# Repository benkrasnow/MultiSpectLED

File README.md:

# MultiSpectLED
Array of 15 1W LEDs spanning 280nm to 940nm

Notes:  The 280nm LED has a forward voltage drop of between 5V and 7.5V depending on the voltage bin.  This is higher that I expected when I designed the circuit, and it will not work if the power supply is really 5.0V.  It should have a boost converter instead of a buck converter.  However, I happened to receive an LED with a 5.1V drop, and my 5V wall adapter supplies 5.35V at 500mA, so the system works with the buck converter, just barely.  This part of the circuit should be redesigned if 280nm is needed.

UPDATE:  I added 0402 resistors near each buck controller.
The "enable" pin on the PAM2804 buck controller is very high-impedance, and will float around while the MCU is being programmed.  This causes bright flashes, and potentially can draw too much current from the supply, so pull-down resistors *MUST* be added between each PWM control line and ground.  I haven't updated the PCB yet, and fixed it in the prototype by adding resistors:

The heatsink has a 45mm wide rasied section, and the PCB is designed so that all exposed copper is ground within this 45mm strip. I used the PCB itself as a drill guide to drill 2.5mm holes, and then tapped them M3.  I used M3x4 screws to hold the PCB to the heatsink.

Originally, I planned to use Luxeon IR LEDs from Lumileds for the 850 and 940nm.  The thermal pad on these is tied to the anode, so it will not work with the current PCB design. I replaced them with alternate parts with very similar footprint, and have updated the BOM and layout.  

Heatsink and fan: https://www.amazon.com/dp/B00006B8EX
The fan runs nice and quiet on 5V, and provides more than enough airflow

USB-C 5V 4A power adapter:  Digikey 1597-106060004-ND  This should have enough current capacity to run up to 8 LEDs at full power.

Each LED channel is configured for 500mA , which is set by the 0.2 ohm resistor and internal 0.1V reference of the buck controller IC, PAM2804.
Dimming is achieved with PWM, and I used "software PWM" to get 15 separate channels from the Teensy-LC.  The SoftPWM library defaults to 60Hz update, which I noticed flickering, so I edited SoftPWM.cpp to use 120Hz instead.  MCUs with 15+ hardware PWM channels exist, but are more expensive, and not easy to find these days!

The Teensy-LC also provides easy programability for external triggering, remote control via USB serial, etc

The +5V power connection on the Teensy-LC between its USB micro plug and Vin pin should be cut.  There is a thin link between two exposed pads on the underside for this purpose.  This allows the Teensy to be powered only by the Vin pin, which is connected to the USB-C power rail in this design (it must be powered for programming).  If the link is not cut, and both USB connections are made with mismatched voltages (eg 4.9V vs 5.3V), bad currents may flow.

Total cost is about $180, and the 280nm LED alone is $24

.

Thermal performance looks very good.  At 16C ambient, the hottest part is the inductor at 23C.

Device was used to create Silver nanoprisms grown into structural colors by high power LEDs

A video can be found here - https://www.youtube.com/watch?v=v8pko9IlFW4

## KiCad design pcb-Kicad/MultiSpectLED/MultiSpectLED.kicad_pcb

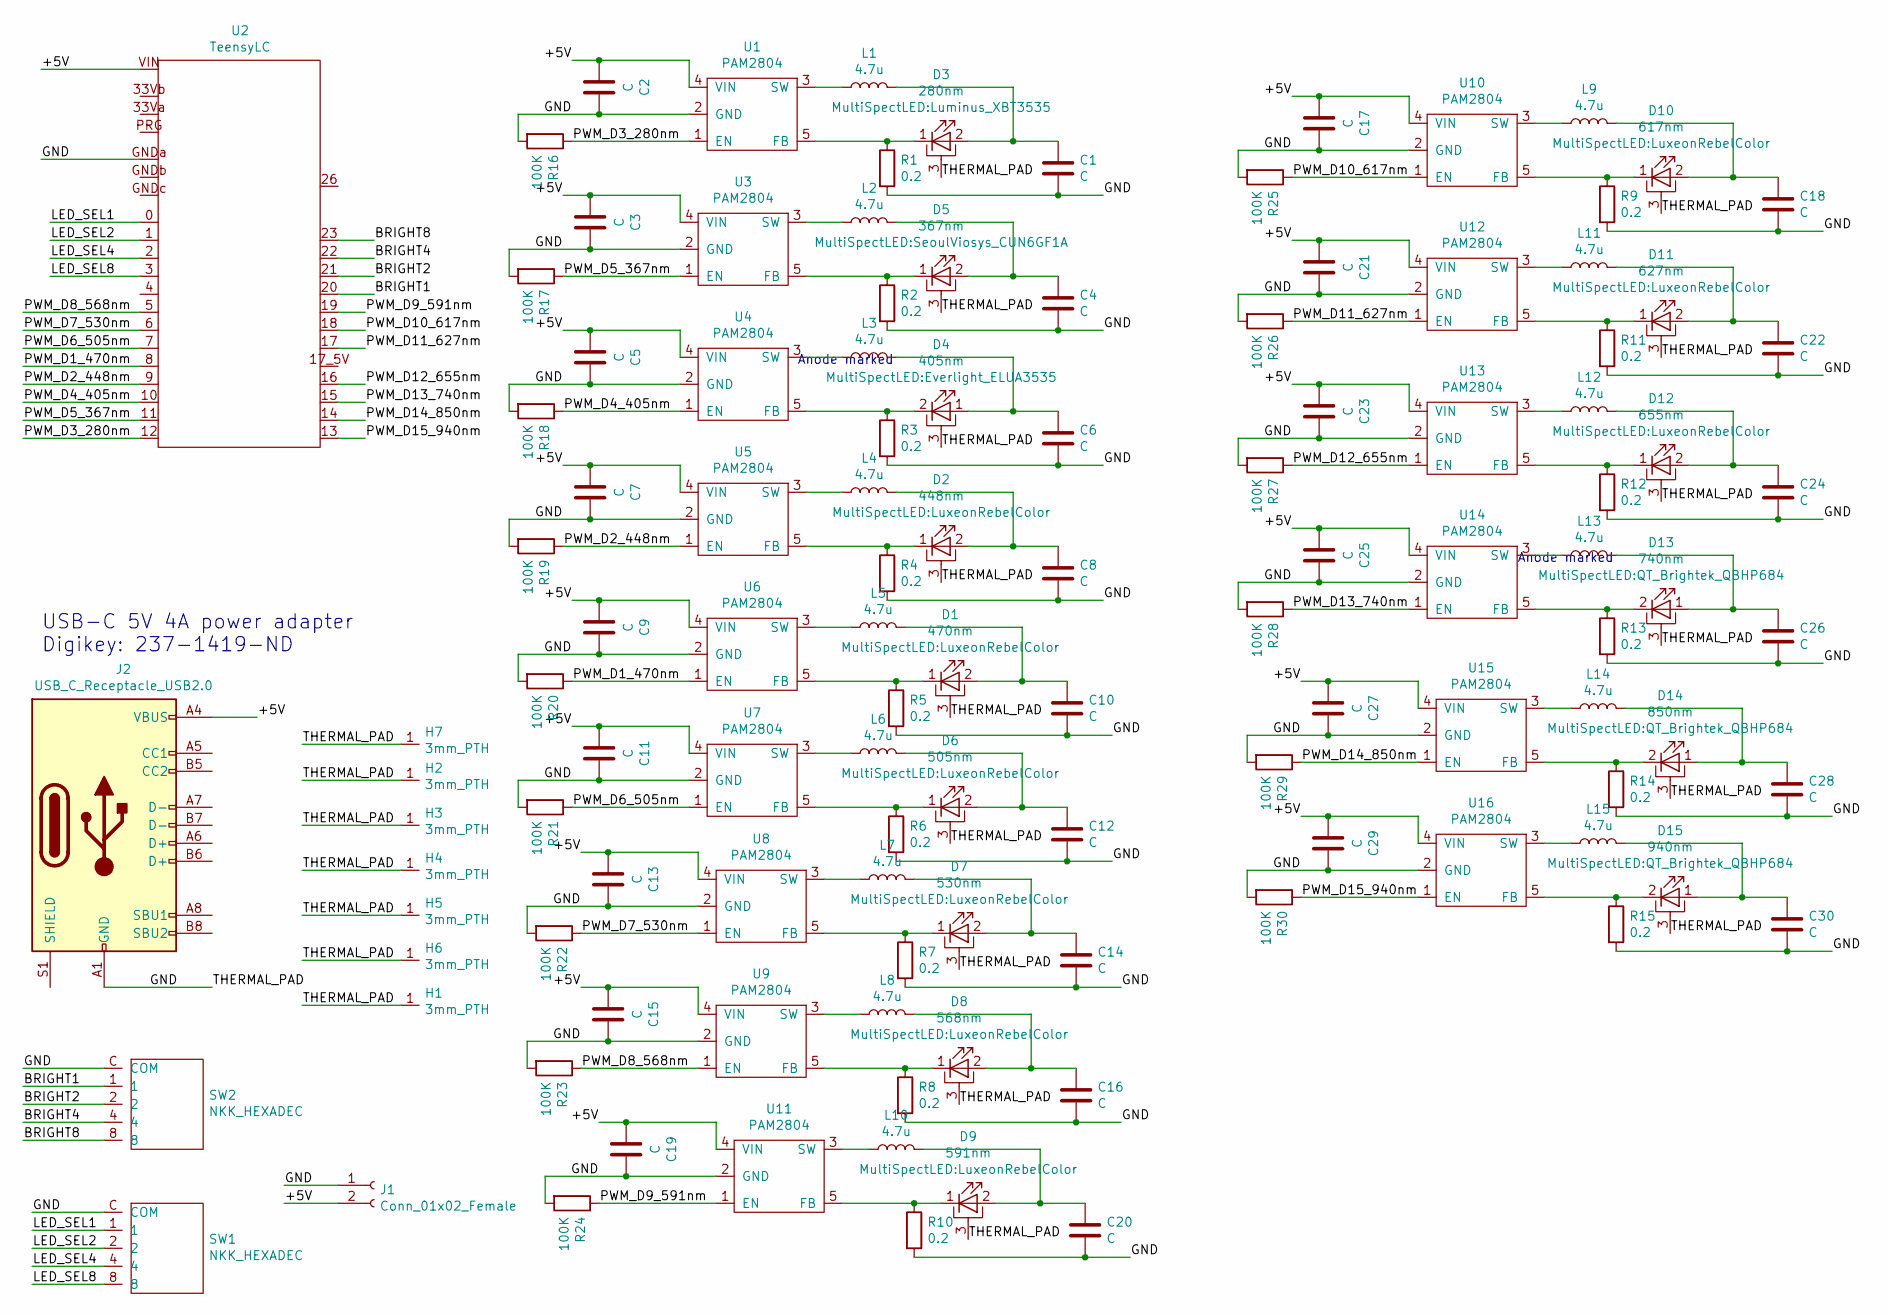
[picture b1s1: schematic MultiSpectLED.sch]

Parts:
C1, C2, C3, C4, C5, C6, C7, C8, C9, C10, C11, C12, C13, C14, C15, C16, C17, C18, C19, C20, C21, C22, C23, C24, C25, C26, C27, C28, C29, C30: C; C_0805_2012Metric; Digikey Part Number 490-3886-1-ND
D1: 470nm; LuxeonRebelColor; Digikey Part Number 1416-1029-1-ND
D2: 448nm; LuxeonRebelColor; Digikey Part Number 1416-1038-1-ND
D3: 280nm; Luminus_XBT3535; Digikey Part Number 1214-XBT-3535-UV-A130-CD270-00CT-ND
D4: 405nm; Everlight_ELUA3535; Digikey Part Number 1080-1620-1-ND
D5: 367nm; SeoulViosys_CUN6GF1A; Digikey Part Number 2112-CUN6GF1ACT-ND
D6: 505nm; LuxeonRebelColor; Digikey Part Number 1416-1031-1-ND
D7: 530nm; LuxeonRebelColor; Digikey Part Number 1416-1036-1-ND
D8: 568nm; LuxeonRebelColor; Digikey Part Number 1416-1185-1-ND
D9: 591nm; LuxeonRebelColor; Digikey Part Number 1416-1027-1-ND
D10: 617nm; LuxeonRebelColor; Digikey Part Number 1416-1026-1-ND
D11: 627nm; LuxeonRebelColor; Digikey Part Number 1416-1024-1-ND
D12: 655nm; LuxeonRebelColor; Digikey Part Number 1416-1701-1-ND
D13: 740nm; QT_Brightek_QBHP684; Digikey Part Number 1516-1213-1-ND
D14: 850nm; QT_Brightek_QBHP684
D15: 940nm; QT_Brightek_QBHP684
H1, H2, H3, H4, H5, H6, H7: 3mm_PTH
J1: Conn_01x02_Female; FAN_PADS
J2: USB_C_Receptacle_USB2.0; USB_C_Receptacle_Amphenol_12401610E4-2A; Digikey Part Number CP-036AHPJCT-ND
L1, L2, L3, L4, L5, L6, L7, L8, L9, L10, L11, L12, L13, L14, L15: 4.7u; L_1007_2518Metric; Digikey Part Number 587-1621-1-ND
R1, R2, R3, R4, R5, R6, R7, R8, R9, R10, R11, R12, R13, R14, R15: 0.2; R_0805_2012Metric; Digikey Part Number RL12S.20FCT-ND
R16, R17, R18, R19, R20, R21, R22, R23, R24, R25, R26, R27, R28, R29, R30: 100K; R_0402_1005Metric; Digikey Part Number RC1005F104CS
SW1, SW2: NKK_HEXADEC; NKK_FR02; Digikey Part Number 360-2543-1-ND
U1, U3, U4, U5, U6, U7, U8, U9, U10, U11, U12, U13, U14, U15, U16: PAM2804; SOT-23-5; Digikey Part Number PAM2804AAB010DICT-ND
U2: TeensyLC; Digikey Part Number 1568-1233-ND

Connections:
/+5V: C2.2, C3.2, C5.2, C7.2, C9.2, C11.2, C13.2, C15.2, C17.2, C19.2, C21.2, C23.2, C25.2, C27.2, C29.2, J1.2, J2.A4 (VBUS), J2.A9 (VBUS), J2.B4 (VBUS), J2.B9 (VBUS), U1.4 (VIN), U2.VIN, U3.4 (VIN), U4.4 (VIN), U5.4 (VIN), U6.4 (VIN), U7.4 (VIN), U8.4 (VIN), U9.4 (VIN), U10.4 (VIN), U11.4 (VIN), U12.4 (VIN), U13.4 (VIN), U14.4 (VIN), U15.4 (VIN), U16.4 (VIN)
/BRIGHT1: SW2.1, U2.20
/BRIGHT2: SW2.2, U2.21
/BRIGHT4: SW2.4, U2.22
/BRIGHT8: SW2.8, U2.23
/GND: C1.2, C2.1, C3.1, C4.2, C5.1, C6.2, C7.1, C8.2, C9.1, C10.2, C11.1, C12.2, C13.1, C14.2, C15.1, C16.2, C17.1, C18.2, C19.1, C20.2, C21.1, C22.2, C23.1, C24.2, C25.1, C26.2, C27.1, C28.2, C29.1, C30.2, D1.3 (PAD), D2.3 (PAD), D3.3 (PAD), D4.3 (PAD), D5.3 (PAD), D6.3 (PAD), D7.3 (PAD), D8.3 (PAD), D9.3 (PAD), D10.3 (PAD), D11.3 (PAD), D12.3 (PAD), D13.3 (PAD), D14.3 (PAD), D15.3 (PAD), H1.1, H2.1, H3.1, H4.1, H5.1, H6.1, H7.1, J1.1, J2.A1 (GND), J2.A12 (GND), J2.B1 (GND), J2.B12 (GND), R1.2, R2.2, R3.2, R4.2, R5.2, R6.2, R7.2, R8.2, R9.2, R10.2, R11.2, R12.2, R13.2, R14.2, R15.2, R16.2, R17.2, R18.2, R19.2, R20.2, R21.2, R22.2, R23.2, R24.2, R25.2, R26.2, R27.2, R28.2, R29.2, R30.2, SW1.C (COM), SW2.C (COM), U1.2 (GND), U2.GNDa, U3.2 (GND), U4.2 (GND), U5.2 (GND), U6.2 (GND), U7.2 (GND), U8.2 (GND), U9.2 (GND), U10.2 (GND), U11.2 (GND), U12.2 (GND), U13.2 (GND), U14.2 (GND), U15.2 (GND), U16.2 (GND)
/LED_SEL1: SW1.1, U2.0
/LED_SEL2: SW1.2, U2.1
/LED_SEL4: SW1.4, U2.2
/LED_SEL8: SW1.8, U2.3
/PWM_D1_470nm: R20.1, U2.8, U6.1 (EN)
/PWM_D2_448nm: R19.1, U2.9, U5.1 (EN)
/PWM_D3_280nm: R16.1, U1.1 (EN), U2.12
/PWM_D4_405nm: R18.1, U2.10, U4.1 (EN)
/PWM_D5_367nm: R17.1, U2.11, U3.1 (EN)
/PWM_D6_505nm: R21.1, U2.7, U7.1 (EN)
/PWM_D7_530nm: R22.1, U2.6, U8.1 (EN)
/PWM_D8_568nm: R23.1, U2.5, U9.1 (EN)
/PWM_D9_591nm: R24.1, U2.19, U11.1 (EN)
/PWM_D10_617nm: R25.1, U2.18, U10.1 (EN)
/PWM_D11_627nm: R26.1, U2.17, U12.1 (EN)
/PWM_D12_655nm: R27.1, U2.16, U13.1 (EN)
/PWM_D13_740nm: R28.1, U2.15, U14.1 (EN)
/PWM_D14_850nm: R29.1, U2.14, U15.1 (EN)
/PWM_D15_940nm: R30.1, U2.13, U16.1 (EN)
unnamed: C1.1, D3.2 (A), L1.2
unnamed: C4.1, D5.2 (A), L2.2
unnamed: C6.1, D4.1 (A), L3.2
unnamed: C8.1, D2.2 (A), L4.2
unnamed: C10.1, D1.2 (A), L5.2
unnamed: C12.1, D6.2 (A), L6.2
unnamed: C14.1, D7.2 (A), L7.2
unnamed: C16.1, D8.2 (A), L8.2
unnamed: C18.1, D10.2 (A), L9.2
unnamed: C20.1, D9.2 (A), L10.2
unnamed: C22.1, D11.2 (A), L11.2
unnamed: C24.1, D12.2 (A), L12.2
unnamed: C26.1, D13.1 (A), L13.2
unnamed: C28.1, D14.1 (A), L14.2
unnamed: C30.1, D15.1 (A), L15.2
unnamed: D1.1 (K), R5.1, U6.5 (FB)
unnamed: D2.1 (K), R4.1, U5.5 (FB)
unnamed: D3.1 (K), R1.1, U1.5 (FB)
unnamed: D4.2 (K), R3.1, U4.5 (FB)
unnamed: D5.1 (K), R2.1, U3.5 (FB)
unnamed: D6.1 (K), R6.1, U7.5 (FB)
unnamed: D7.1 (K), R7.1, U8.5 (FB)
unnamed: D8.1 (K), R8.1, U9.5 (FB)
unnamed: D9.1 (K), R10.1, U11.5 (FB)
unnamed: D10.1 (K), R9.1, U10.5 (FB)
unnamed: D11.1 (K), R11.1, U12.5 (FB)
unnamed: D12.1 (K), R12.1, U13.5 (FB)
unnamed: D13.2 (K), R13.1, U14.5 (FB)
unnamed: D14.2 (K), R14.1, U15.5 (FB)
unnamed: D15.2 (K), R15.1, U16.5 (FB)
unnamed: L1.1, U1.3 (SW)
unnamed: L2.1, U3.3 (SW)
unnamed: L3.1, U4.3 (SW)
unnamed: L4.1, U5.3 (SW)
unnamed: L5.1, U6.3 (SW)
unnamed: L6.1, U7.3 (SW)
unnamed: L7.1, U8.3 (SW)
unnamed: L8.1, U9.3 (SW)
unnamed: L9.1, U10.3 (SW)
unnamed: L10.1, U11.3 (SW)
unnamed: L11.1, U12.3 (SW)
unnamed: L12.1, U13.3 (SW)
unnamed: L13.1, U14.3 (SW)
unnamed: L14.1, U15.3 (SW)
unnamed: L15.1, U16.3 (SW)

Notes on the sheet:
Anode marked
USB-C 5V 4A power adapter Digikey: 237-1419-ND

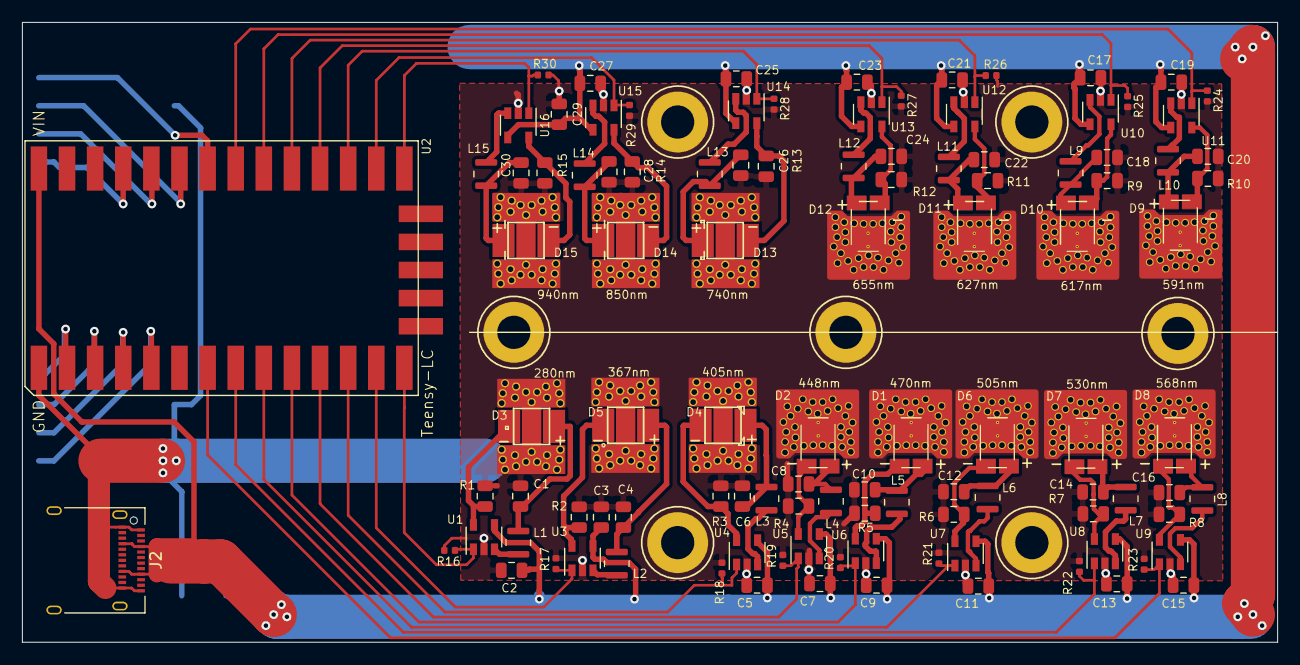
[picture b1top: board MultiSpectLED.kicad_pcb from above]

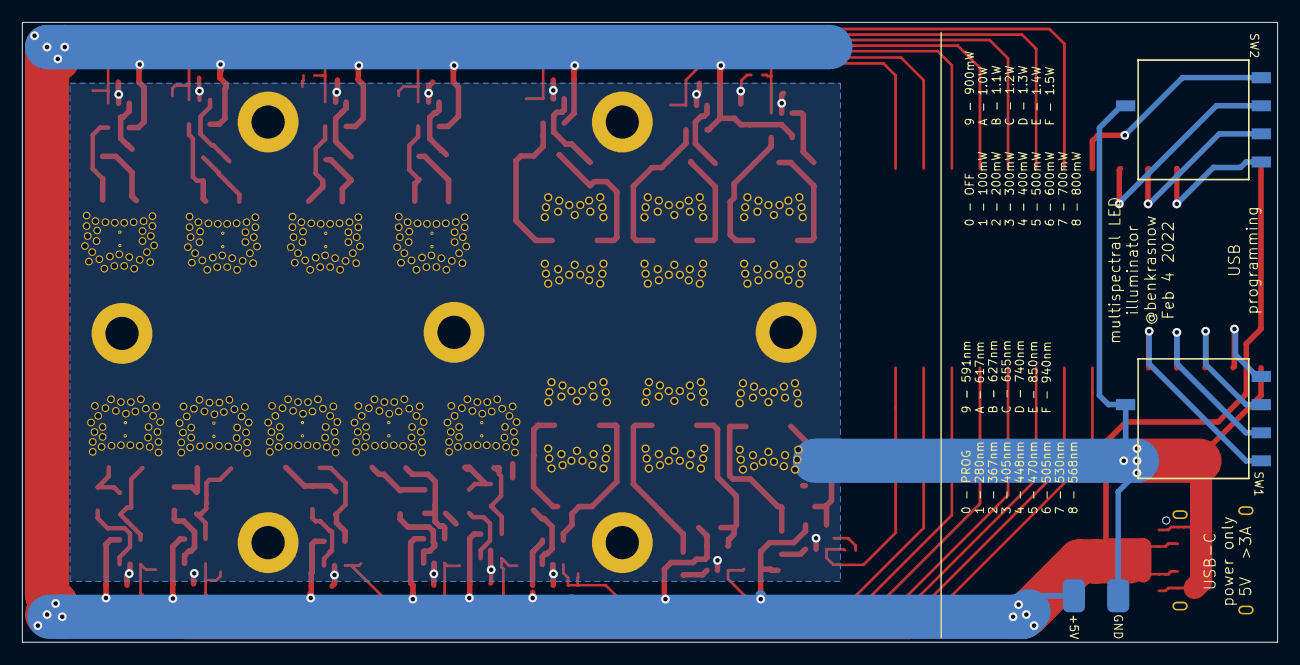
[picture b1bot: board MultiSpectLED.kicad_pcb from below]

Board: 2 copper layers, 113.4 x 56.0 mm, 117 parts (3 on the bottom side), 70 nets.

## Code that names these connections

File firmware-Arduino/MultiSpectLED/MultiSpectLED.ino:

#include <SoftPWM.h>   //The library normally uses a 60Hz update rate which is defined in Arduino/hardware/teensy/avr/libraries/SoftPWM/SoftPWM.cpp


#define TWOPI 6.2832
#define PIOVERTWO 1.5708

#define PIN_LED_940 13
#define PIN_LED_850 14
#define PIN_LED_740 15
#define PIN_LED_655 16
#define PIN_LED_627 17
#define PIN_LED_617 18
#define PIN_LED_591 19
#define PIN_LED_568 5
#define PIN_LED_530 6
#define PIN_LED_505 7
#define PIN_LED_470 8
#define PIN_LED_448 9
#define PIN_LED_405 10
#define PIN_LED_367 11
#define PIN_LED_280 12


#define PIN_SEL1 0
#define PIN_SEL2 1
#define PIN_SEL4 2
#define PIN_SEL8 3

#define PIN_BRIGHT1 20
#define PIN_BRIGHT2 21
#define PIN_BRIGHT4 22
#define PIN_BRIGHT8 23

uint8_t led_array_pwm[15];
uint8_t led_array_pins[15] = {PIN_LED_280, PIN_LED_367, PIN_LED_405, PIN_LED_448, PIN_LED_470, PIN_LED_505, PIN_LED_530, PIN_LED_568, PIN_LED_591, PIN_LED_617, PIN_LED_627, PIN_LED_655, PIN_LED_740, PIN_LED_850, PIN_LED_940};
float cur_phase = 0;

void setup() {
  Serial.begin(9600);
  
   SoftPWMBegin();

   pinMode(PIN_SEL1, INPUT_PULLUP);
   pinMode(PIN_SEL2, INPUT_PULLUP);
   pinMode(PIN_SEL4, INPUT_PULLUP);
   pinMode(PIN_SEL8, INPUT_PULLUP);
   pinMode(PIN_BRIGHT1, INPUT_PULLUP);
   pinMode(PIN_BRIGHT2, INPUT_PULLUP);
   pinMode(PIN_BRIGHT4, INPUT_PULLUP);
   pinMode(PIN_BRIGHT8, INPUT_PULLUP);

   clear_all_leds();
}

void loop() {
  uint8_t cur_brightness = map(ReadLEDBrightness(),0,15,10,255);
  uint8_t cur_selection = ReadLEDSelection();
  
  clear_all_leds();
  
  cur_phase = (cur_phase > 7) ? -10 : cur_phase+0.08;
  
  if(cur_selection == 0)
  {
    for(int i = 0; i<15;i++)
      {
        led_array_pwm[i] = 255 * sine_pulse(cur_phase + i);      
      }
  }
  
  if(cur_selection > 0 && cur_selection < 16)
    {
      led_array_pwm[cur_selection-1] = cur_brightness;
    }
  update_leds();
  delay(16);
}




float sine_pulse(float input)  {
  if(input < 0)
    {
      return 0;
    }
  else if(input > TWOPI)
  {
    return 0;
  }
  else
  {
    return (1+sin(input-PIOVERTWO))/2;
  }
}

void update_leds(void)  {
  for(int i = 0; i<15;i++)
   {
    SoftPWMSet(led_array_pins[i], led_array_pwm[i]);
   }
}


void clear_all_leds(void)  {
  for(int i = 0; i<15;i++)
    {
      led_array_pwm[i] = 0;
    }
}


uint8_t ReadLEDSelection(void)  {
  uint8_t result = 0;
  result += !digitalRead(PIN_SEL1)<<0;
  result += !digitalRead(PIN_SEL2)<<1;
  result += !digitalRead(PIN_SEL4)<<2;
  result += !digitalRead(PIN_SEL8)<<3;
  return result; 
}


uint8_t ReadLEDBrightness(void)  {
  uint8_t result = 0;
  result += !digitalRead(PIN_BRIGHT1)<<0;
  result += !digitalRead(PIN_BRIGHT2)<<1;
  result += !digitalRead(PIN_BRIGHT4)<<2;
  result += !digitalRead(PIN_BRIGHT8)<<3;
  return result; 
}

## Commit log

2022-02-19 Added photos, pcb, and firmware
2022-02-20 Cost estimate was too high because I ordered extras
2022-02-20 Added pulldown resistors on each PAM2804 enable line
2022-04-10 feat: Adds initial link to video
    If merged would resolve #2
